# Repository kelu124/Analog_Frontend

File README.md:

# Analog Frontend PCB
This folder contains the design files for the analog circuitry required for a single channel of an ultrasound imaging system. 

Schematic:  
  
See the `drawings` folder for a high-resolution PDF version.

PCB:  
  
See the `drawings` folder for a full resolution PDF version, including each layer individually.

### Bill of Materials
See `Analog_Frontend.html`.

### Changelog
* `v1.0` Initial design
* `v1.1` 
* `v1.2` 
* `v1.3` Added a row of header pins and silkscreened labels
* `v1.3-doc` Added documentation
* `v2.0` Minitiarized design
* `v2.1b` Single transistor transmitter
* `v2.2_op1` Single transistor transmitter with higher output power
* `v2.2_op2` Push-pull transmitter using DMN2004K and DMP2004K MOSFETs
* `v2.2_op3` (Work in Progress) Transmitter using the MD1213 and TC6320 ultrasound transmitter chips

Each version can be accessed in this repository through the git tag system. 

### Credits
Designed by William Meng, Cindy Xiao, and Ruoyu Sheng.

The VGA subcircuit design was adapted from the [AD8331 evaluation board](http://www.analog.com/media/en/technical-documentation/evaluation-documentation/154207235AD8331EB_a.pdf). 

Community-developed KiCAD symbols and models:

* [SMA footprint](https://github.com/rascalmicro/rascalmicro-kicad-footprints.pretty/blob/master/SMA.kicad_mod)
* [SOT-523 footprint](https://github.com/cpavlina/kicad-pcblib/blob/master/smd-semi.pretty/SOT-523.kicad_mod)
* [Teensy symbols](https://github.com/XenGi/teensy_library) and [Teensy footprints](https://github.com/XenGi/teensy.pretty)

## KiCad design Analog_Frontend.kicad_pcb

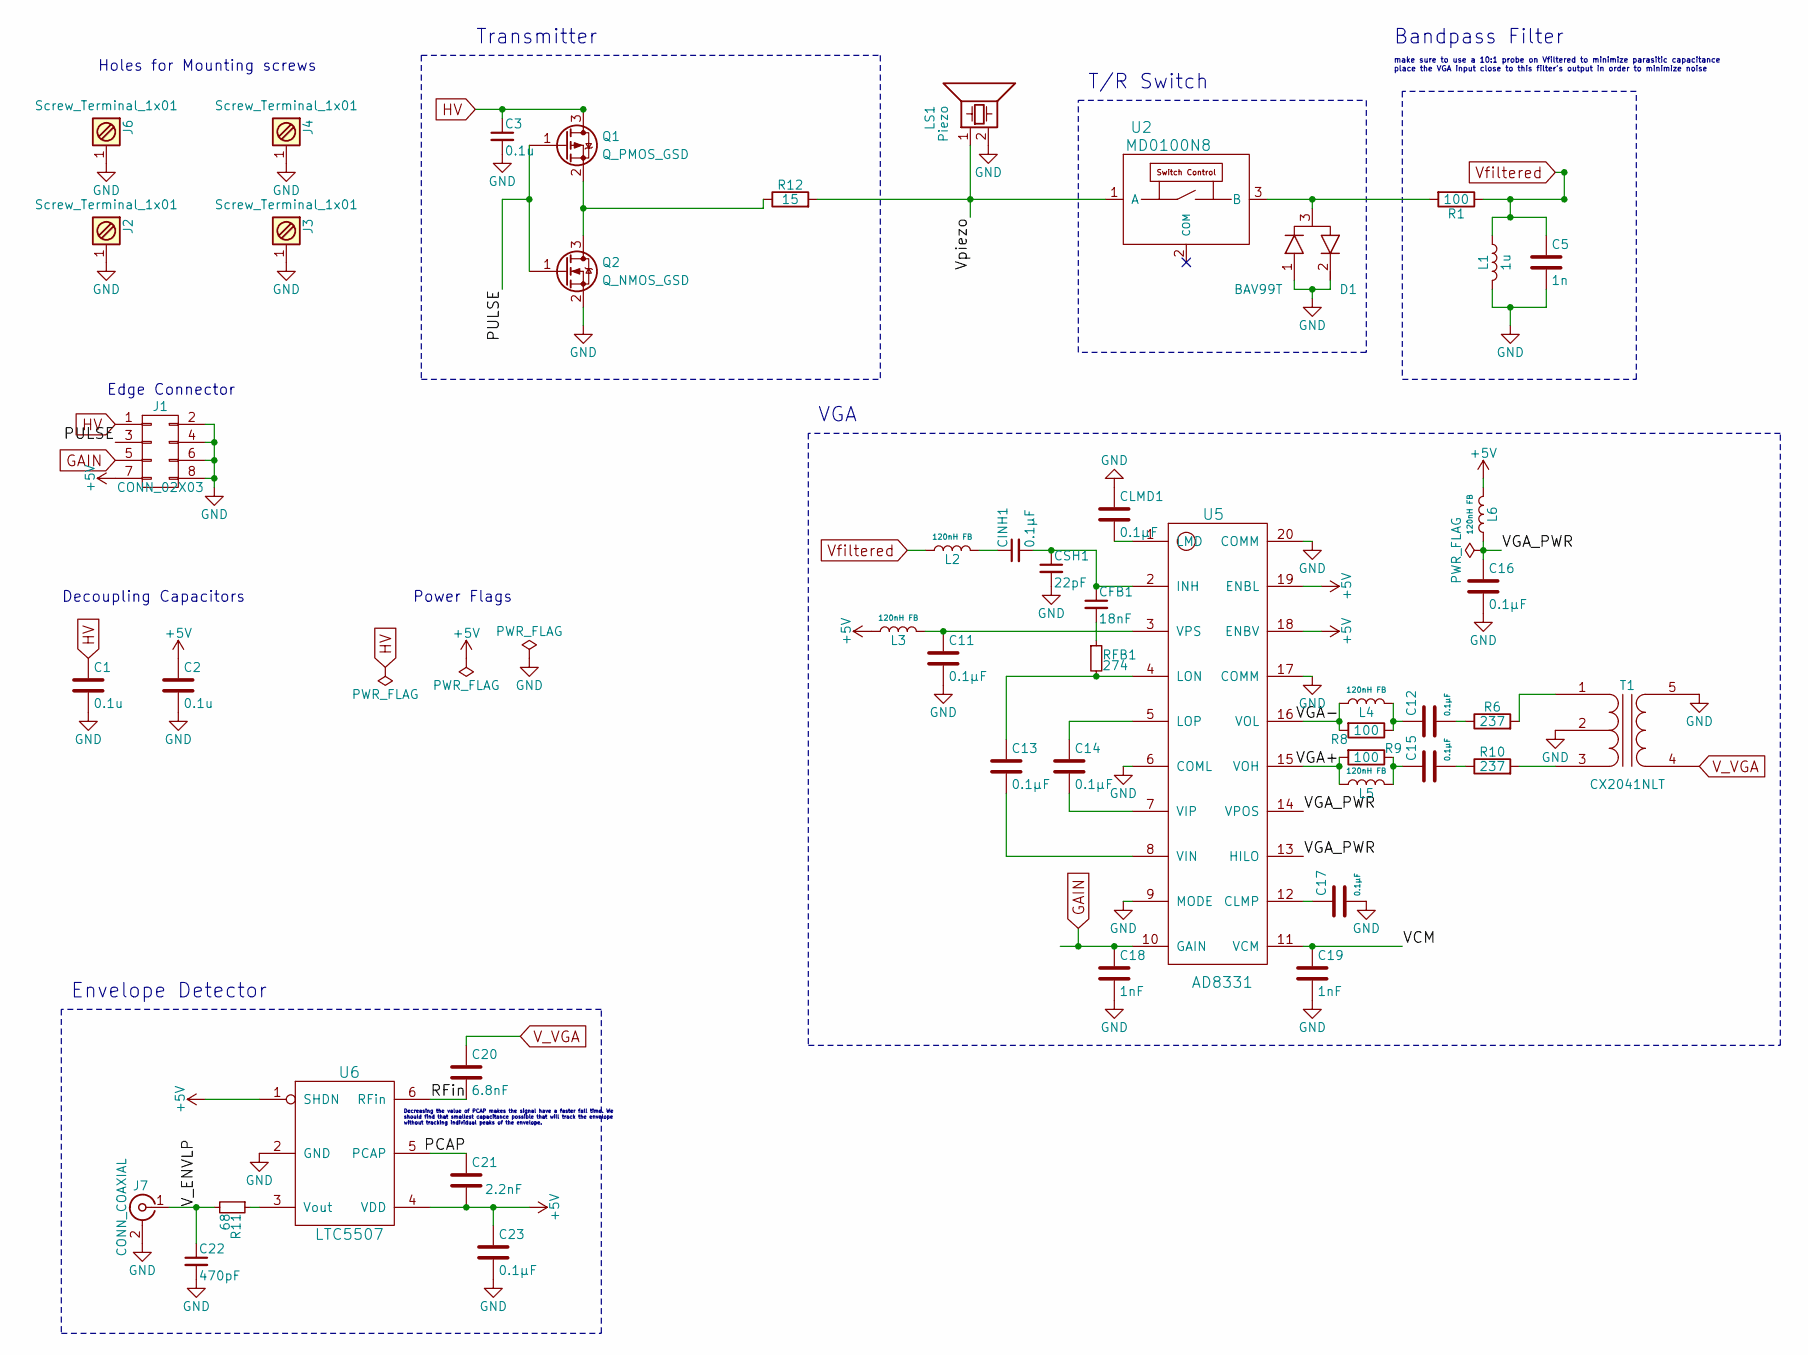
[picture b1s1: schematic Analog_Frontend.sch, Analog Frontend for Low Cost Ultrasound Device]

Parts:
C1, C2, C3: 0.1u; C_0603
C5: 1n; C_0603
C11, C12, C13, C14, C15, C16, C17, C23: 0.1µF; C_0603
C18, C19: 1nF; C_0603
C20: 6.8nF; C_0603
C21: 2.2nF; C_0603
C22: 470pF; C_0603
CFB1: 18nF; C_0603
CINH1: 0.1µF; C_0603
CLMD1: 0.1µF; C_0603
CSH1: 22pF; C_0603
D1: BAV99T; SOT-523
J1: CONN_02X03; Pin_Header_Angled_2x04_Pitch2.54mm
J2, J3, J4, J6: Screw_Terminal_1x01; MountingHole_3.2mm_M3
J7: CONN_COAXIAL; SAM8857-ND
L1: 1u; L_0603
L2, L3, L4, L5, L6: 120nH FB; R_0603
LS1: Piezo; Pin_Header_Angled_1x02_Pitch2.54mm
Q1: Q_PMOS_GSD; SOT-23
Q2: Q_NMOS_GSD; SOT-23
R1: 100; R_0805
R6, R10: 237; R_0603
R8, R9: 100; R_0603
R11: 68; R_0805
R12: 15; R_0603
RFB1: 274; R_0603
T1: CX2041NLT
U2: MD0100N8; SOT89-3_Housing_Handsoldering
U5: AD8331; QSOP-20_3.9x8.6mm_Pitch0.64mm
U6: LTC5507; TSOT-23-6_MK06A

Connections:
+5V: C2.1, C21.2, C23.1, J1.7, L3.1, L6.2, U5.18 (ENBV), U5.19 (ENBL), U6.1 (SHDN), U6.4 (VDD)
/PCAP: C21.1, U6.5 (PCAP)
/PULSE: J1.3, Q1.1 (G), Q2.1 (G)
/RFin: C20.2, U6.6 (RFin)
/VCM: C19.1, U5.11 (VCM)
/VGA+: L5.1, R9.2, U5.15 (VOH)
/VGA-: L4.1, R8.2, U5.16 (VOL)
/VGA_PWR: C16.1, L6.1, U5.13 (HILO), U5.14 (VPOS)
/V_ENVLP: C22.1, J7.1 (In), R11.2
/Vpiezo: LS1.1, R12.2, U2.1 (A)
GAIN: C18.1, J1.5, U5.10 (GAIN)
GND: C1.2, C2.2, C3.2, C5.2, C11.2, C16.2, C17.2, C18.2, C19.2, C22.2, C23.2, CLMD1.1, CSH1.2, D1.1 (A), D1.2 (K), J1.2, J1.4, J1.6, J1.8, J2.1, J3.1, J4.1, J6.1, J7.2 (Ext), L1.2, LS1.2, Q2.2 (S), T1.2 (PM), T1.5 (S2), U5.6 (COML), U5.9 (MODE), U5.17 (COMM), U5.20 (COMM), U6.2 (GND)
HV: C1.1, C3.1, J1.1, Q1.3 (D)
unnamed: C11.1, L3.2, U5.3 (VPS)
unnamed: C12.1, L4.2, R8.1
unnamed: C12.2, R6.1
unnamed: C13.1, RFB1.2, U5.4 (LON)
unnamed: C13.2, U5.8 (VIN)
unnamed: C14.1, U5.5 (LOP)
unnamed: C14.2, U5.7 (VIP)
unnamed: C15.1, L5.2, R9.1
unnamed: C15.2, R10.1
unnamed: C17.1, U5.12 (CLMP)
unnamed: CFB1.1, CINH1.2, CSH1.1, U5.2 (INH)
unnamed: CFB1.2, RFB1.1
unnamed: CINH1.1, L2.2
unnamed: CLMD1.2, U5.1 (LMD)
unnamed: D1.3 (common), R1.2, U2.3 (B)
unnamed: Q1.2 (S), Q2.3 (D), R12.1
unnamed: R6.2, T1.1 (PR1)
unnamed: R10.2, T1.3 (PR2)
unnamed: R11.1, U6.3 (Vout)
V_VGA: C20.1, T1.4 (S1)
Vfiltered: C5.1, L1.1, L2.1, R1.1

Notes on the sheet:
make sure to use a 10:1 probe on Vfiltered to minimize parasitic capacitance place the VGA input close to this filter's output in order to minimize noise
VGA
Transmitter
Bandpass Filter
T/R Switch
Decreasing the value of PCAP makes the signal have a faster fall time. We should find that smallest capacitance possible that will track the envelope without tracking individual peaks of the envelope.
Edge Connector
Envelope Detector
Holes for Mounting screws
Decoupling Capacitors
Power Flags

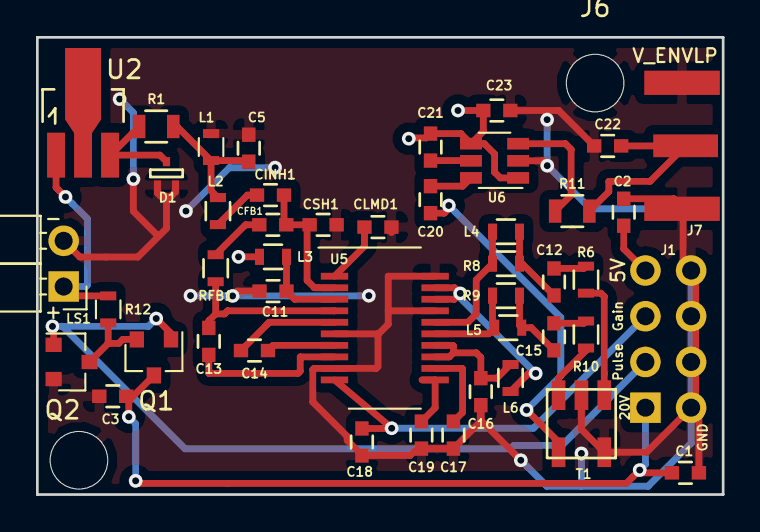
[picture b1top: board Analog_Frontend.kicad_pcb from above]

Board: 2 copper layers, 38.1 x 25.4 mm, 47 parts (1 on the bottom side), 34 nets.

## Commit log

2017-05-20 Replaced spaces with underscores in folder name
2017-06-05 Added +5V plane on B.Cu layer
2017-06-06 Added BOM document in HTML format. See https://www.hashdefineelectronics.com/kicad-bom-wizard for instructions on how to generate this file.
2017-06-07 Added stencil file for v1.1, to be cut on Othermill with 30 degree bit
2017-06-08 Decreased value of PCAP value to speed up fall time of envelope detector.
2017-06-14 Fixed SMA footprint to match the dimensions of the SMA connectors we purchased from uxcell
2017-06-14 Removed redundant traces and vias for +5V net since we now have a +5V plane
2017-06-14 Flipped L1 to be on B.Cu layer
2017-06-15 Added some silkscreen labels
2017-06-16 Made the silkscreened references visible and moved them around to improve readability
2017-06-16 Added 6 pin header at top of the board
2017-06-16 Cleaned up all the F.SilkS reference labels and re-routed output stage of VGA to have more spacing between components.
2017-06-16 Changed footprint of C1 from 1206 ceramic to 3216 tantalum; added OSHW logo; fixed regression with SMA connector footprints
2017-06-16 Changed solder paste clearance to -3mil
2017-06-16 PCB v1.3
2017-06-19 Updated metadata for PCB v1.3
2017-06-21 Added documentation for everything
2017-07-18 BOM for Analog Frontend PCB v1.3
2017-08-02 resize board v2.0
    replace through hole parts, change board to 1*2
2017-09-29 Analog Board V2.1
2017-09-29 Fixed 5V net label in schematic
2017-09-29 Added decoupling capacitors and right angle connector footprints
2017-10-02 2。1 modified Oct.1
2017-10-02 Updated silkscreen labels
2017-10-02 Fixed footprint for edge-mounted SMA connector so that the copper is no longer covered by solder mask.
2017-10-02 Updated labels and generated Gerber files for v2.1b
2017-10-19 Analog BOM & Nucleo pins added
2017-11-02 added inductor & res
2017-11-03 meow
2017-11-03 inducer placed
2017-11-03 gerber files
2017-11-03 fixed 0805
2017-11-07 Fixed rotation of SOT-23 footprint for Q2
2017-11-07 Q2 footprint change, connect ground plane
2017-11-12 changed schematic and imported netlist
2017-11-12 footprint change
2017-11-12 removed inductor
2017-11-12 change wire connection
2017-11-12 try to add new chips
2017-11-12 worked on schematic
2017-11-12 QFN footprint
2017-11-12 trivial change
2017-11-13 change some wire connections
2017-11-17 Fixed pinouts of Q1 and Q2. Also optimized connections and ground plane, and switched M3 holes to the standard footprint.
2017-11-17 Optimized ground plane and renamed 20V to HV
2017-11-17 Gerber files for v2.2_op2
2017-11-17 Fixed extraneous holes for v2.2_op2
2017-12-01 Retroactively fixed v2.2_op1 label and updated component 3D orientations for KiCad v4.0.7
2017-12-01 Retroactively updated date and 3D orientation of connectors for v2.2_op2
2018-03-14 Updated README and pictures
